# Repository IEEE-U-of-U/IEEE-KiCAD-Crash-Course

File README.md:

# IEEE KiCAD Crash Course Fall 2025

## Introduction
Welcome to the IEEE KiCAD Crash Course for Fall 2025 at the University of Utah!

## General Information

We will be hosting this workshop over 4 weeks this semester, currently scheduled for **Tuesdays at 4:00 PM to 5:30 PM** beginning September 30th and ending Oct 28th (see tentative schedule below). The intended groups are any interested student organizations at the University of Utah such as USR, UCubeSat, and FSAE.

The workshops will be held in **WEB 2470** unless otherwise specified.

We will be presenting a design for a *USB-C Breadboard Power Supply* and all participants are invited to participate in designing their own PCBs.

__Workshop Goals__

- Introduction to PCB design
- Introduction to ECAD software (KiCAD)
- Introduction to Schematic Layout
- Introduction to PCB Layout

## ECAD Software

### KiCAD

Please install KiCAD if you are not using Altium. While we do support this program, as KiCAD can import Altium files, we will be focusing on Altium Designer.

KiCAD Official Page:
https://www.kicad.org/

## Schedule

| DATE   | SESSION Title | LINK |
|--------|---------------|------|
| Sep 30 | Introduction to Schematics | [Week 01](https://github.com/IEEE-U-of-U/IEEE-KiCAD-Crash-Course/tree/main/Week01) |
| Oct 14 | Symbols and Components | [Week 02](https://github.com/IEEE-U-of-U/IEEE-KiCAD-Crash-Course/tree/main/Week02) |
| Oct 21 | Introduction to PCB Layout | [Week 03](https://github.com/IEEE-U-of-U/IEEE-KiCAD-Crash-Course/tree/main/Week03) |
| Oct 28 | Extra Session (If Necessary) | [Week 04](https://github.com/IEEE-U-of-U/IEEE-KiCAD-Crash-Course/tree/main/Week04) |

While it is recommended to attend all sessions, we will provide the design and workshop files through a GitHub repository. To stay up to date, please be sure to follow along to not fall behind.

## Schematic

## Contact Info

- Questions may be routed to the IEEE email: ieee.studentbranch.uofu@gmail.com
- Updates are also posted on the IEEE / ECE discord: https://discord.gg/TMjhuDCCfy

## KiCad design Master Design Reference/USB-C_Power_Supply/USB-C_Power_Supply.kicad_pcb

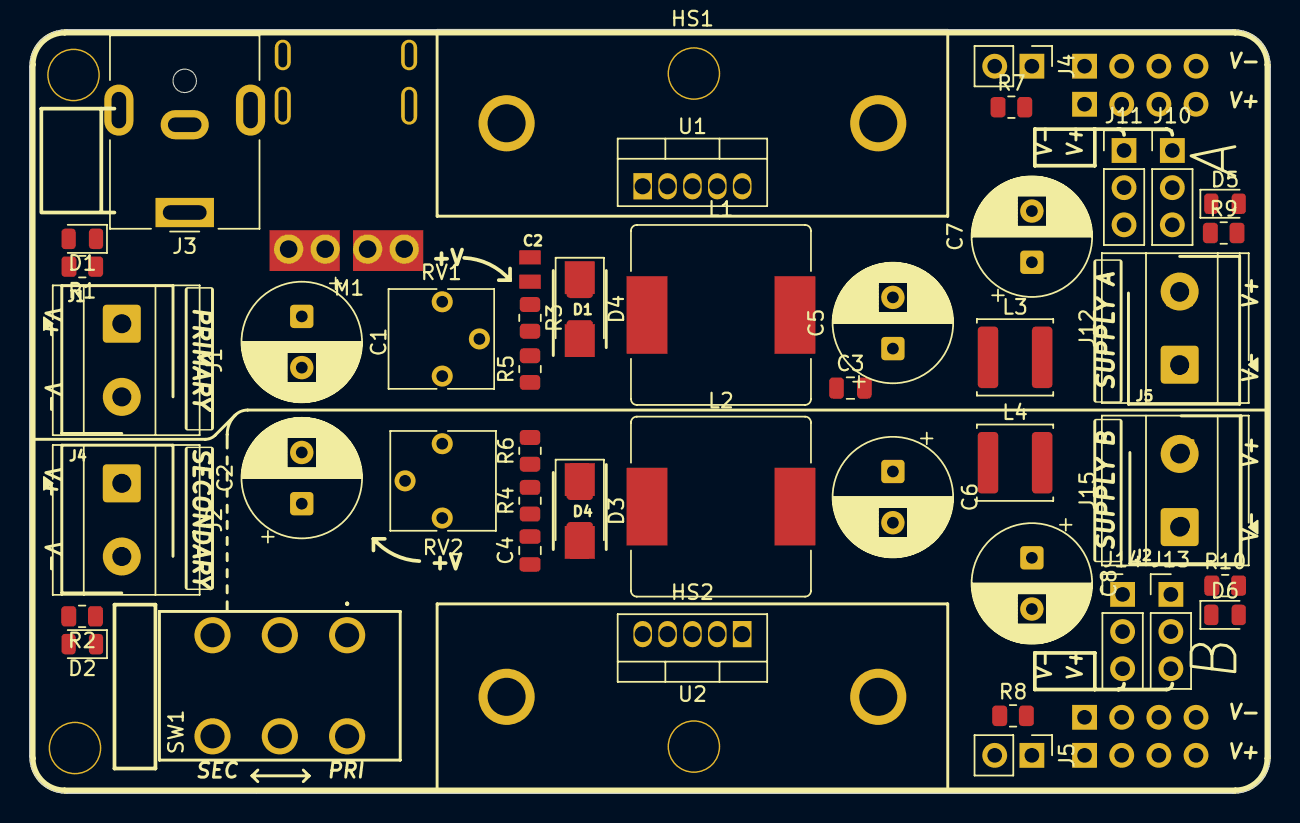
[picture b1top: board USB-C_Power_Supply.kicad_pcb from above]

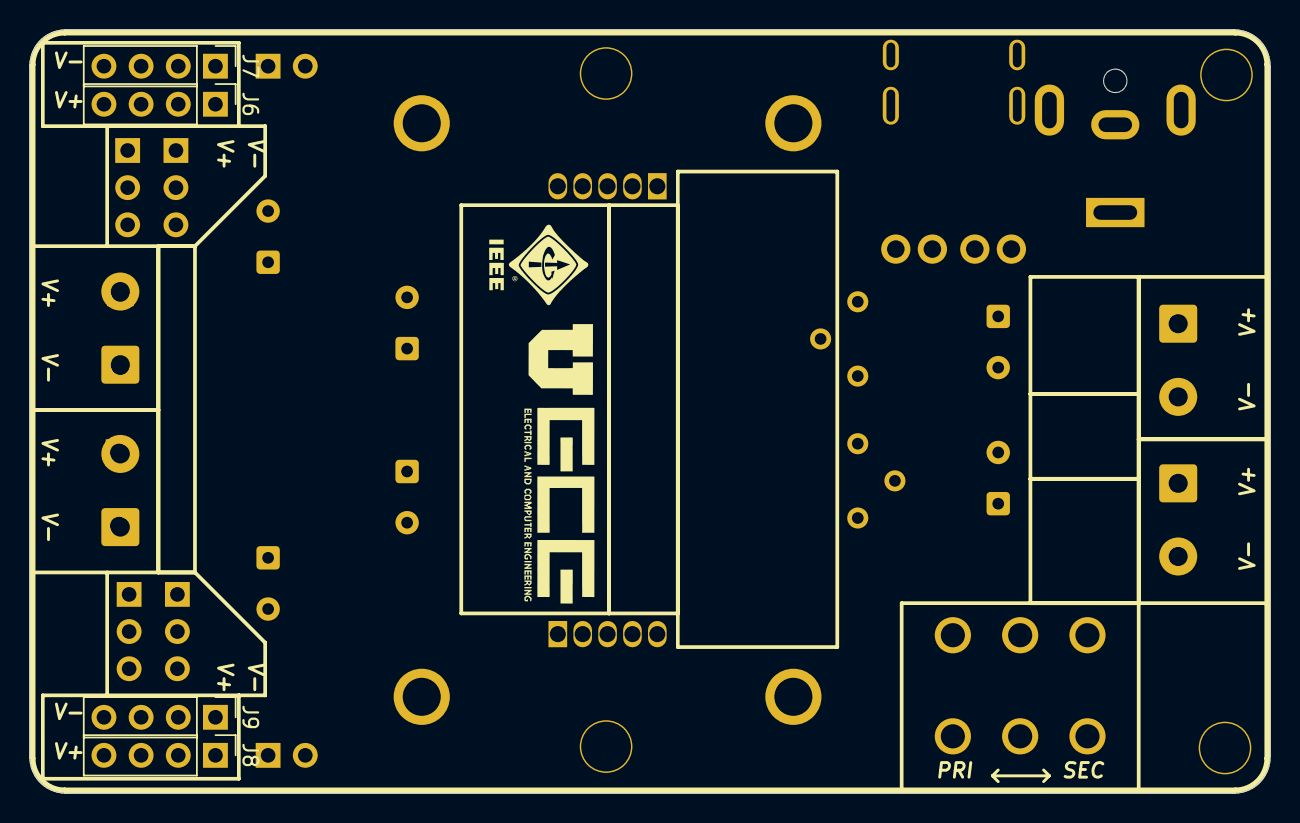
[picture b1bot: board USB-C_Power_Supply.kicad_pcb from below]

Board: 2 copper layers, 84.8 x 52.2 mm, 58 parts (4 on the bottom side), 24 nets, no tracks yet.

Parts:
C1, C2: 270u; CP_Radial_D8.0mm_P3.50mm
C2#2: 100n; CAP0805
C3, C4: 100n; C_0805_2012Metric
C5, C6, C7, C8: 470u; CP_Radial_D8.0mm_P3.50mm
D1, D2, D5, D6: LED; LED_0805_2012Metric
D1#2, D4: SS510B; DO-214AC (SMA)
D3, D4#2: D_Schottky; D_SMA
HS1, HS2: 637-10ABPE; 63710ABPE
J1, J2, J12, J15: 691137710002; TerminalBlock_Phoenix_MKDS-1,5-2_1x02_P5.00mm_Horizontal
J1#2, J2#2, J4, J5: 691137710002; SHDR2W70P0X500_1X2_1000X750X1160P
J3: Barrel_Jack; BarrelJack_CUI_PJ-063AH_Horizontal
J4#2, J5#2: Conn_01x02_Pin; PinHeader_1x02_P2.54mm_Vertical
J6, J7, J8, J9: Conn_01x04_Pin; PinHeader_1x04_P2.54mm_Vertical
J10, J11, J13, J14: Conn_01x03_Pin; PinHeader_1x03_P2.54mm_Vertical
L1, L2: 100u; L_Bourns_SRR1210A
L3, L4: 22u; L_APV_ANR5020
M1: USB-PD; USB_C-PD
R1, R2, R7, R8, R9, R10: 3.3k; R_0805_2012Metric
R3, R4, R5, R6: 1k; R_0805_2012Metric
RV1, RV2: 10k; Potentiometer_Vishay_T73YP_Vertical
SW1: SW_DPDT_x2; GF1260305
U1, U2: LM2576T-ADJ; TO-220-5_Vertical

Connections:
+VCC_A: C7.1, J2#2.1, J4#2.1, J12.1, L3.2, R9.1
+VCC_B: C8.1, J5.1, J5#2.1, J8.1, J8.2, J8.3, J8.4, J13.1, J13.2, J13.3, J15.1, L4.2, R10.1
GND_A: C1.2, C2#2.2, C3.2, C5.2, C7.2, D1.1 (K), D1#2.2, D3.2 (A), D5.1 (K), J1.2, J1#2.1, J2#2.2, J3.2, J7.1, J7.2, J7.3, J7.4, J11.1, J11.2, J11.3, J12.2, M1.2 (V-), R3.1, R7.2, SW1.4 (A), U1.3 (GND), U1.5 (~ON/OFF)
GND_B: C2.2, C4.2, C6.2, C8.2, D4.2, D4#2.2 (A), D6.1 (K), J5.2, J9.1, J9.2, J9.3, J9.4, J14.1, J14.2, J14.3, J15.2, R4.1, R8.2, SW1.5 (B), U2.3 (GND), U2.5 (~ON/OFF)
unnamed: C5.1, L1.2, L3.1, R5.2
unnamed: C6.1, L2.2, L4.1, R6.2
unnamed: D1.2 (A), R1.2
unnamed: D2.2 (A), R2.2
unnamed: D3.1 (K), L1.1, U1.2 (OUT)
unnamed: D4#2.1 (K), L2.1, U2.2 (OUT)
unnamed: D5.2 (A), R9.2
unnamed: D6.2 (A), R10.2
unnamed: J4#2.2, R7.1
unnamed: J5#2.2, R8.1
unnamed: J6.1, J6.2, J6.3, J6.4
unnamed: J10.1, J10.2, J10.3
unnamed: R5.1, RV1.1
unnamed: R6.1, RV2.1
unnamed: R3.2, RV1.2, RV1.3, U1.4 (FB)
unnamed: R4.2, RV2.2, RV2.3, U2.4 (FB)
SEC_GND: D2.1 (K), J2.2, J4.1
V_IN_A: C1.1, C2#2.1, C3.1, J1.1, J1#2.2, J3.1, M1.1 (V+), R1.1, SW1.1 (A), U1.1 (VIN)
V_IN_B: C2.1, C4.1, SW1.2 (B), U2.1 (VIN)
V_IN_SEC: J2.1, J4.2, R2.1, SW1.3 (C)

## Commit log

2025-10-01 Added Week01 Resources
2025-10-07 Bro first commit
2025-10-14 Week02 Resources
2025-10-15 Week02 Task
2025-10-21 Week03
